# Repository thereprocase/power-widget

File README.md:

# Power Widget

**Canonical KiCad schematic.** This image is exported from the [native editable schematic](hardware/bench-rev-a/power-widget-bench.kicad_sch). The [earlier drawing was a layout mockup](hardware/bench-rev-a/layout-mockup.svg), not a KiCad export or the design authority.

**Reusable agent prompt, including the original inspiration:**

> think through the layout and topology from the perspective of a brilliant 1980s electrical engineer who stayed current on everything straight through to 2026. use his brain to architect the sheet and make it gorgeous
>
> Create a complete, flat, single-sheet schematic from this project's authoritative circuit data. Make the page explain the circuit: power and signal flow, measurement branches, isolation boundaries, supplies and service controls. Use traditional electrical symbols, continuous wires, explicit junction dots and unambiguous crossings: wire hops where supported, otherwise the native tool’s undotted-crossing convention. Keep every component and numbered pin accounted for; annotate wires with net names instead of replacing connections with labels. Preserve the circuit exactly. Use deliberate placement, readable typography and restrained color, with the clarity of a classic service-manual foldout. Verify connectivity against the source, export a zoomable SVG and printable PDF, put the image at the top of the README, and commit and push the result.
>
> Use conventional schematic symbols that engineers recognize on sight: ANSI-style zigzag resistors; parallel-plate nonpolarized capacitors and explicitly marked polarized capacitors; coil inductors; diode anode/cathode symbols with the cathode bar; LEDs with outward light arrows and photodiodes with inward light arrows; normally open or normally closed switch contacts shown in their unactuated state; connector pins, jumper links and test points; four-terminal Kelvin shunts with separate force and sense terminals; and, where present, BJT base/collector/emitter and emitter arrows, MOSFET gate/drain/source and body diodes, and op-amp triangles with +/− inputs. Use functional IC rectangles with named and numbered pins. Distinguish signal common, chassis ground and protective earth; preserve separate isolated returns. Use these symbols only for the devices and functions actually present. Verify each symbol's device type, terminal mapping, polarity, arrow direction and default state against the circuit data and the manufacturer's pinout. Rotate or mirror symbols only while preserving their electrical meaning. A wire crossing is not a junction unless explicitly dotted; a graphic must never imply an unintended connection. Check the rendered drawing as well as its underlying netlist.
>
> Implement the layout in the canonical, editable source of the design system this project actually uses: for KiCad, the native schematic in the existing KiCad project. Preserve component identities, footprints, pin mappings and PCB associations. Export the README image and PDF directly from that native source, and run the design system's electrical checks plus schematic-to-PCB consistency checks. Ensure the normal regeneration workflow cannot overwrite the native design with a competing source of truth. A separately drawn SVG or diagram is only a mockup, even if its netlist matches; label any intermediate mockup explicitly and do not present it as the canonical schematic.
>
> Make component identity and wire continuity obvious. Prefer one physical component in one location. If splitting a component improves the page, use the convention of a civil-engineering matchline: ghost the omitted portion at each location, mark the matchline, and add explicit reciprocal notes naming the other section and exactly where to look. Never leave the reader to infer that two symbols are one part or guess where a connection went. Use small cloud callouts to explain potentially confusing features; keep annotations visually distinct from electrical symbols and wires.
>
> Keep all lettering clear of conductors: never run a wire through a net name, reference, value, pin label or note. Place ordinary wire labels above or beside the wire with visible clearance; put boxed net tags on short annotation stubs in open space. Preserve the continuous main wire and use an explicit junction at each stub. Check the actual native export, not just the underlying coordinates or netlist. Visually inspect every functional section at readable magnification, including both ends of each connection, pin numbers, component values, junctions, crossings, polarity, symbol orientation and callouts. Then review the whole sheet for flow and consistency. Keep lettering clear of other lettering, symbol graphics (including LED arrows), and dashed graphical boundaries too. Add automated rendered-text/wire and text/text overlap checks where possible, and fix every collision before publishing.

**The whole circuit on one sheet:** [native SVG export](hardware/bench-rev-a/single-sheet.svg) · [printable A2 PDF](hardware/bench-rev-a/single-sheet.pdf) · [drawing notes and reproduction](hardware/bench-rev-a/README.md#single-sheet-schematic). All 82 physical components and 65 named nets. Each component appears once, including the complete J1 and P1 connectors. Dots identify connections; undotted crossings do not connect. Cloud notes explain the through path and Kelvin sensing.

An inline USB-C power monitor with isolated PC reporting. Preserve the original charger and cable negotiation while measuring voltage, current, watts and Wh.

**Newest design: [bench revision A native KiCad project](hardware/bench-rev-a/README.md).** It includes the sensing circuit, isolated USB reporting, STM32 firmware/debug access, assigned footprints and a routed bench PCB. Native KiCad checks report **zero ERC violations, DRC violations, unconnected items and schematic/PCB mismatches**. See the [layout review](docs/layout-review.md) for evidence and open gates. **The selected USB population is 5 A maximum; the project’s 9 A USB assembly is still a sourcing and qualification gate.**

## Board preview and drawings

Actual KiCad 2D plot of the **125 × 107 mm** bench PCB. The reporting USB-C port is on the lower long edge. This is an unbuilt prototype design; no 3D assembly render or hardware photographs are available yet.

| View | Contents |
|---|---|
| [PCB views](hardware/bench-rev-a/README.md#pcb-views) | Top and bottom copper plots from the routed board |
| [Circuit drawings](hardware/bench-rev-a/README.md#circuit-drawings) | Canonical single-sheet KiCad schematic, native exports and layout notes |
| [Architecture diagram](docs/architecture.md#two-power-domains-and-a-passive-main-path) | Transparent power path, sensing and isolated PC reporting |
| [Editable KiCad project](hardware/bench-rev-a/power-widget-bench.kicad_pro) | Schematic, PCB and local symbol/footprint libraries in the same directory |

## Design target

| Item | Requirement |
|---|---|
| Voltage | 28 V DC; at least 33.6 V component design margin |
| Continuous current | **9 A target: documented laptop maximum 8.5 A + 0.5 A** |
| Current design margin | **10.8 A: 1.20 × the 9 A target** |
| Inline data | USB 2.0; retain other contacts for charging transparency |
| Power accuracy | ±1% of reading at ≥5 W; ±5% from 0.5 W to below 5 W |
| Acquisition | About 58 fresh pairs/s, time-weighted one-second V/A/W reports and accumulated Wh |
| Reporting | Isolated USB-C on a long edge; timestamped serial, optional PC MQTT/HTTP forwarding |
| Product | Cheap but good; no display, battery or standalone logger required |

The selected [Apple/Dell/Lenovo laptop roster](docs/manufacturer-modes.md) drives the target. Extreme proprietary phone charging is excluded. The original 10 A/full-EPR and later 6 A specifications are superseded; voltage remains 28 V. No physical assembly is qualified yet.

## Early open question: captive male or two receptacles?

**Captive male is the bench baseline; final product topology remains open.** The original charger cable enters one receptacle, and a short custom captive plug extends its contacts to the device. The separate PC receptacle is on a long edge. OEM MagSafe/slim-tip cables may require charger-side placement and different energy accounting.

Two inline receptacles remain an allowed outcome if their orientation and cable-discovery behavior can be made transparent. Fixed CC wiring between two ordinary C-to-C cables fails some orientations; the [contact map and truth table](docs/connector-routing.md) explain the constraint. A generic cut cable is not a qualified captive assembly.

## Bench circuit and calculated feasibility

INA228 measures a 5 mΩ four-terminal high-side shunt. An inline LDO powers sensing; a PC-powered STM32F072CBT6 communicates through isolated I²C. The board includes SWD, UART, GPIO, force/Kelvin access and selectable floating sensor power. Dedicated links support measuring board consumption. Original charging contacts have no inline PD controller or substituted contract.

| Calculation | Preliminary result |
|---|---|
| Largest one-second DC error allocation, ≥5 W | **0.874%**, at 28 V / 5 W |
| Largest one-second DC error allocation, 0.5–<5 W | **4.539%**, at 28 V / 0.5 W |
| Sensor window / reporting | **17.28 ms / one second** |
| Added hot loop resistance, captive study | **14.879 mΩ** against a 15 mΩ target |
| Shunt heat at 9 A / 10.8 A | **0.405 W / 0.583 W** nominal |

These are engineering allocations, not measured specifications. One-second noise, dynamic energy accuracy, thermal behavior and connector performance require physical validation. A board-output reading needs a downstream cable correction before being called laptop-input energy.

## Design package

| Read | Purpose |
|---|---|
| [Design brief](docs/design-brief.md) | Current requirements and assumptions |
| [Bench hardware](hardware/bench-rev-a/README.md) | Circuit sheets, component schedule, jumpers and bring-up |
| [Manufacturer modes](docs/manufacturer-modes.md) | Primary laptop evidence and rating rule |
| [Connector wiring](docs/connector-routing.md) | Contact map and orientation proof |
| [Architecture](docs/architecture.md) / [decisions](docs/decisions.md) | Components, domains and unresolved gates |
| [Calculated budgets](analysis/results.md) / [method](docs/budgets.md) | Accuracy, loss, timing and assumptions |
| [Firmware contract](firmware/README.md) | MCU pins, sensor registers, timestamped serial and integration plan |
| [Energy comparison](docs/energy-comparison.md) | Matching intervals, board consumption, cable correction and uncertainty |
| [Validation](docs/validation-plan.md) / [cost and build](docs/cost-and-build.md) | Prototype qualification and planning allowances |
| [Research record](docs/sources.md) / [progress](docs/progress.md) | Sources, evidence gaps and checkpoints |

## Reproduce

```sh
python tools/budgets.py --check
python tools/orientations.py --check
python tools/capture_bench.py --check
python tools/draw_flat_schematic.py --check
```

Omit `--check` to regenerate. The budget and orientation tools use the Python standard library. Native schematic export/check commands require KiCad 9+ and librsvg; see [CAD reproduction](hardware/bench-rev-a/README.md#single-sheet-schematic). The budget sweep covers 19,635 settled operating points at the 9 A target. `capture_bench.py` exports and validates native pin/net data; `draw_flat_schematic.py` also runs KiCad ERC and PCB DRC with schematic parity.

## Next gate

Review the routed PCB against a fabricator's stack and capabilities, finalize the orderable BOM and captive strain relief, and resolve protection/overrange behavior before fabrication release. Source and qualify the required 9 A USB assembly; the selected USB parts support only the 5 A bench population. Firmware can start on the documented interfaces while these gates close. Physical validation must establish thermal capacity, measurement accuracy and OEM charging compatibility. Earlier designs remain in commit history.

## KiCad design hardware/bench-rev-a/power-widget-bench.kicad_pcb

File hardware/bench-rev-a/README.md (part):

# Bench revision A — native schematic and PCB

**28 V / 9 A continuous design target, 10.8 A design margin. No physical assembly is qualified.** This is the accessible prototype for connector experiments, calibration and MCU firmware development. It contains the complete proposed sensing, reporting, supply and debug circuits rather than a separate continuity fixture.

Open [power-widget-bench.kicad_pro](power-widget-bench.kicad_pro) in KiCad 9. The project includes the [native schematic](power-widget-bench.kicad_sch), [editable PCB](power-widget-bench.kicad_pcb), project symbols, and a snapshot of all 23 used footprint types. Native checks report **zero [ERC violations](erc.rpt), [DRC violations, unconnected items and schematic/PCB mismatches](drc.rpt)**. Read the [layout review](../../docs/layout-review.md) for board status and release gates. There are no fabrication-release Gerbers.

## PCB views

These are actual 2D plots exported from the checked-in KiCad PCB. No 3D assembly render or physical prototype photograph is available yet.

[Open top view](pcb-top.svg) — front copper with front silkscreen and outline.

<details>
<summary>Show bottom copper view</summary>

[Open bottom copper view](pcb-bottom.svg) — bottom copper with front silkscreen and outline, **viewed from the top**. This is not a mirrored bottom assembly drawing.

</details>

## Circuit drawings

### Single-sheet schematic

[Native SVG export](single-sheet.svg) · [A2 PDF](single-sheet.pdf) · [Editable schematic](power-widget-bench.kicad_sch) · [Native checks](single-sheet-check.json)

**This is the canonical KiCad schematic, not a separately drawn diagram.** The SVG and PDF are direct `kicad-cli` exports. The README PNG is only a white-background rasterization of that SVG so it remains readable in light and dark themes. The [earlier layout mockup](layout-mockup.svg) is retained as a reference, explicitly not the design authority. The former five-sheet schematic is superseded and remains available in Git history.

The force path runs left to right through R1, with its Kelvin measurement branch directly beneath it. Every J1 and P1 contact is visible in its **one complete connector symbol**. Isolated I²C crosses the marked boundary into the PC-powered reporting circuit. Cloud callouts explain the through path and the shunt's separate force and sense terminals. Every connection is wired continuously. Each net is named once on a short annotation stub, with visible clearance between the tag and conductors. The main wire remains continuous and the stub has an explicit junction. Dots mean junctions; undotted crossings are not connected. Unconnected pin numbers and their no-connect crosses appear inside the relevant packages. There are no off-sheet connections or split component units in this version.

KiCad reports **82 physical components, 65 named nets, 288 connected numbered pins and 30 unconnected numbered pins**. Six additional nonphysical power flags stay in the native schematic for ERC. The [migration comparison](native-migration-check.json) verifies unchanged pin/net connectivity, values, footprints and component UUIDs against the previous native design. PCB edits only flatten the 82 schematic association paths; copper, placement and all other PCB content are unchanged. Native [ERC](erc.rpt), [DRC and schematic/PCB parity](drc.rpt) pass with zero violations or unconnected items.

**Edit `power-widget-bench.kicad_sch` in KiCad.** The local `Bench.kicad_sym` library contains editable native symbol geometry; symbols are also embedded in the schematic. Reference, Value and Footprint are native fields. The auxiliary Domain, Section, CircuitKind, SourceFootprint and Notes fields supply metadata for the JSON and component-schedule exports. The historical JSON `sheet` field now identifies a functional placement group, not a separate schematic sheet.

The normal workflow flows in one direction: **native schematic → native netlist / JSON / schedule / SVG / PDF / PNG**. Neither export script writes a schematic, library or PCB. There is no separate Python circuit definition that can overwrite edits made in KiCad.

```sh
python tools/capture_bench.py             # export JSON and component schedule from KiCad
python tools/draw_flat_schematic.py       # run ERC/DRC/parity and export drawings
python tools/capture_bench.py --check     # verify native data exports are current
python tools/draw_flat_schematic.py --check
```

Use KiCad 9.0.9 and librsvg (`rsvg-convert`) to reproduce the checked-in exports. `KICAD_CLI` can name a local CLI executable. If no local KiCad CLI is found, the tools use Docker and the pinned [official KiCad container](https://gitlab.com/kicad/packaging/kicad-docker) for 9.0.9 in [kicad_native.py](../../tools/kicad_native.py); only the project directory is mounted, and the container runs as the invoking user without network access. `KICAD_DOCKER_IMAGE` can select another installed image. The exporter checks the actual plotted glyph bounds of all visible lettering—including all 65 net labels, references, values, pin labels and notes—against every native wire and against other lettering, rejecting wire/text and text/text collisions. Visual review additionally covers symbol graphics, dashed boundaries, and every functional section at readable magnification. The SVG check ignores only KiCad's export timestamp; the PDF, PNG and native reports have recorded hashes. Print the PDF at A2 or enlarge it, or zoom the vector files on screen.

These are CAD consistency results, not hardware qualification. The existing component, connector and fabrication gates still apply.

## Bench arrangement

The bench PCB is **125 × 107 mm**, four layers, with a candidate 2 oz outer / 1 oz inner stack. The force path runs across the upper portion. The PC receptacle sits on the bottom long edge, and a 3 mm copper keepout separates PC and inline domains across every layer. U2 bridges the gap; the ground plane is split by domain. This is functional isolation, not a certified insulation rating. Fabricator capability, thermal behavior and USB signal integrity require qualification.

J1 is the selected GCT inline receptacle; P1 is the board-side solder termination for a custom captive harness. Its individual contact wiring is defined in [connector-routing.md](../../docs/connector-routing.md). All CC-contact, SBU and SuperSpeed contact paths are retained; only USB 2.0 data performance is in scope. No inline PD controller, new e-marker, or charger-identification termination is fitted. The selected GCT USB population is limited to **5 A**. See [connector selection](../../docs/connector-selection.md); the 9 A USB assembly remains unsourced. Final product topology remains open.

| Access | Connections / use |
|---|---|
| J2 / J3 | Two-pin force connections: 1 = VBUS_A / VBUS_B, 2 = GND_INLINE. Electrically parallel with USB ports; use qualified terminals and short heavy leads. |
| J4 | 1 = upstream shunt Kelvin, 2 = downstream shunt Kelvin, 3 = PCB_B voltage, 4 = quiet inline ground. Sense only. |
| TP4 / TP5 | Separate A5 / B5 contact probes. Use suitable high-impedance, low-capacitance isolated probes; no grounded PC wire. |
| J5 | PC-side I²C: 1 = GND_PC, 2 = switched 3.3 V reference, 3 = SCL, 4 = SDA. External open-drain master supported with U3 held in reset and JP4 fitted. |
| J6 | Inline I²C: 1 = GND_INLINE, 2 = 3V3_INLINE, 3 = SCL, 4 = SDA. Floating instruments only. |
| J7 | Floating external supply: 1 = 3.3 V input, 2 = GND_INLINE. Current limit for initial bring-up; never tie to PC ground. |
| J9 | Cortex 10-pin SWD, 1.27 mm, keyed pin 7 absent. Pin 1 is target-voltage reference; pin 6 has no SWO. |
| J10 | 3.3 V UART: 1 = GND_PC, 2 = board TX, 3 = board RX, 4 = supply reference. |
| J11 | GPIO: GND_PC, 3V3_PC, PA4, PA5, PA6, PA7, PB10, PB11 in pin order. |

Header supply pins are references/outputs except the explicitly identified J7 input. External debug probes must not inject supply power. Grounded bench supplies, scopes and electronic loads can externally join the domains even when the board itself is isolated.

## Jumpers and power accounting

| Link | Normal state | Bench purpose |
|---|---|---|
| JP1 | One shunt on 1–2 | Selects inline LDO. Move the single shunt to 2–3 for floating external J7 supply; never fit both. |
| JP2 | Fitted | Replace with an ammeter to characterize PC-domain consumption. Input capacitor, ESD and VBUS divider are ahead of this link; use a USB input-current measurement for total PC-port draw. |
| JP3 | Fitted | Replace with a floating ammeter to measure the inline regulator/sensor branch. R10 remains in circuit. |
| JP4 | Not fitted | Forces isolator PC supply on for an external I²C master. Remove for normal firmware/suspend testing. R26 limits conflict with PA1. |

U4 derives sensor power from VBUS_A before the shunt. JP3 measures the main self-consumption branch; output-sense loading remains a separate small burden. The current 8 mA allocation is **not** a measured correction. Characterize actual draw over voltage, activity and temperature, including the measuring instrument's burden. See [energy comparison](../../docs/energy-comparison.md).

U7 switches U2 side 1 and its pull-ups using MCU PA1. The ISO1641 side-1 high-state maximum is 3.2 mA at 3.3 V, so simply sleeping the MCU would leave an excessive suspend burden. Before disabling U7, firmware releases PB6/PB7 and removes internal pull-ups; resume enables the rail and waits for settling before I²C. This circuit addresses the identified load; total USB suspend current still needs measurement.

## Bring-up sequence on this board

1. Close the documented PCB/connector/protection release gates, then inspect the assembly unpowered. Verify PC/inline isolation, both independent CC paths and no supply shorts. Leave OEM equipment disconnected.
2. Power J8 only. Establish 3V3_PC, reset/boot/SWD and USB enumeration. Verify PA1 can switch the isolator rail and that suspend removes its load. Sensor absence is a valid diagnostic state.
3. Use current-limited floating 3.3 V at J7 with JP1 on 2–3. Verify INA228 ID, raw readings, calibration commands and logging while VBUS is zero. This permits firmware work before an inline charger is attached.
4. Apply current-limited 5 V through qualified J2/J3 force wiring and a small known load. Verify polarity, the B voltage reference, one-second statistics and energy. Return JP1 to 1–2 and repeat with normal sensor power. Compare the JP3 measurement with the supply budget.
5. Sweep voltage and load for calibration. Increase core current toward 9 A only with rated force connections, monitored temperatures and an appropriately limited supply/load. The 10.8 A point needs an explicit continuous-capacity thermal test; it is not a brief survival pulse.
6. Qualify the actual captive assembly electrically and thermally, then compare direct versus inserted OEM charging across all orientations. Keep the controlled bench at known ≤28 V until overrange handling is resolved.

## Before PCB release

J1 and the force terminals now have selected parts and footprints; P1 has a board-side captive-harness termination. The shunt's four terminals and native pad/net mapping have been reviewed. Complete the orderable BOM, passive voltage/power and capacitor bias/stability review, actual captive assembly and strain relief. The selected USB parts remain limited to 5 A; sourcing a qualified 9 A USB assembly is a separate open gate.

Review the routed board against the fabricator's stack, copper weight, fine clearances and USB impedance requirements. Resolve inline ESD/overrange protection without compromising CC or low-power leakage. Review unpowered behavior, USB timing/current and regulator thermals; physical tests must establish measurement accuracy, current capacity and charging compatibility. See the [layout](../../docs/layout-review.md), [connector](../../docs/connector-selection.md) and [protection](../../docs/protection-review.md) reviews for the remaining work.

Export circuit data from the native schematic with `python tools/capture_bench.py`; use `--check` to detect stale exports. Its assertions check independent CC nets, no shared PC/inline nets and the MCU supply pins. These checks do not replace ERC, impedance/thermal layout work or hardware tests.

## Physical-design reproduction

With KiCad 9 Python `pcbnew` available:

```sh
python tools/capture_bench.py
python tools/footprint_bench.py
python tools/layout_bench.py
python tools/fanout_bench.py
# Route the generated DSN with a compatible Specctra router; use one optimization thread.
python tools/finish_bench.py --session hardware/bench-rev-a/power-widget-bench.ses
# The retained session requires these reviewed manual repairs:
python tools/review_route_bench.py
python tools/finish_bench.py
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
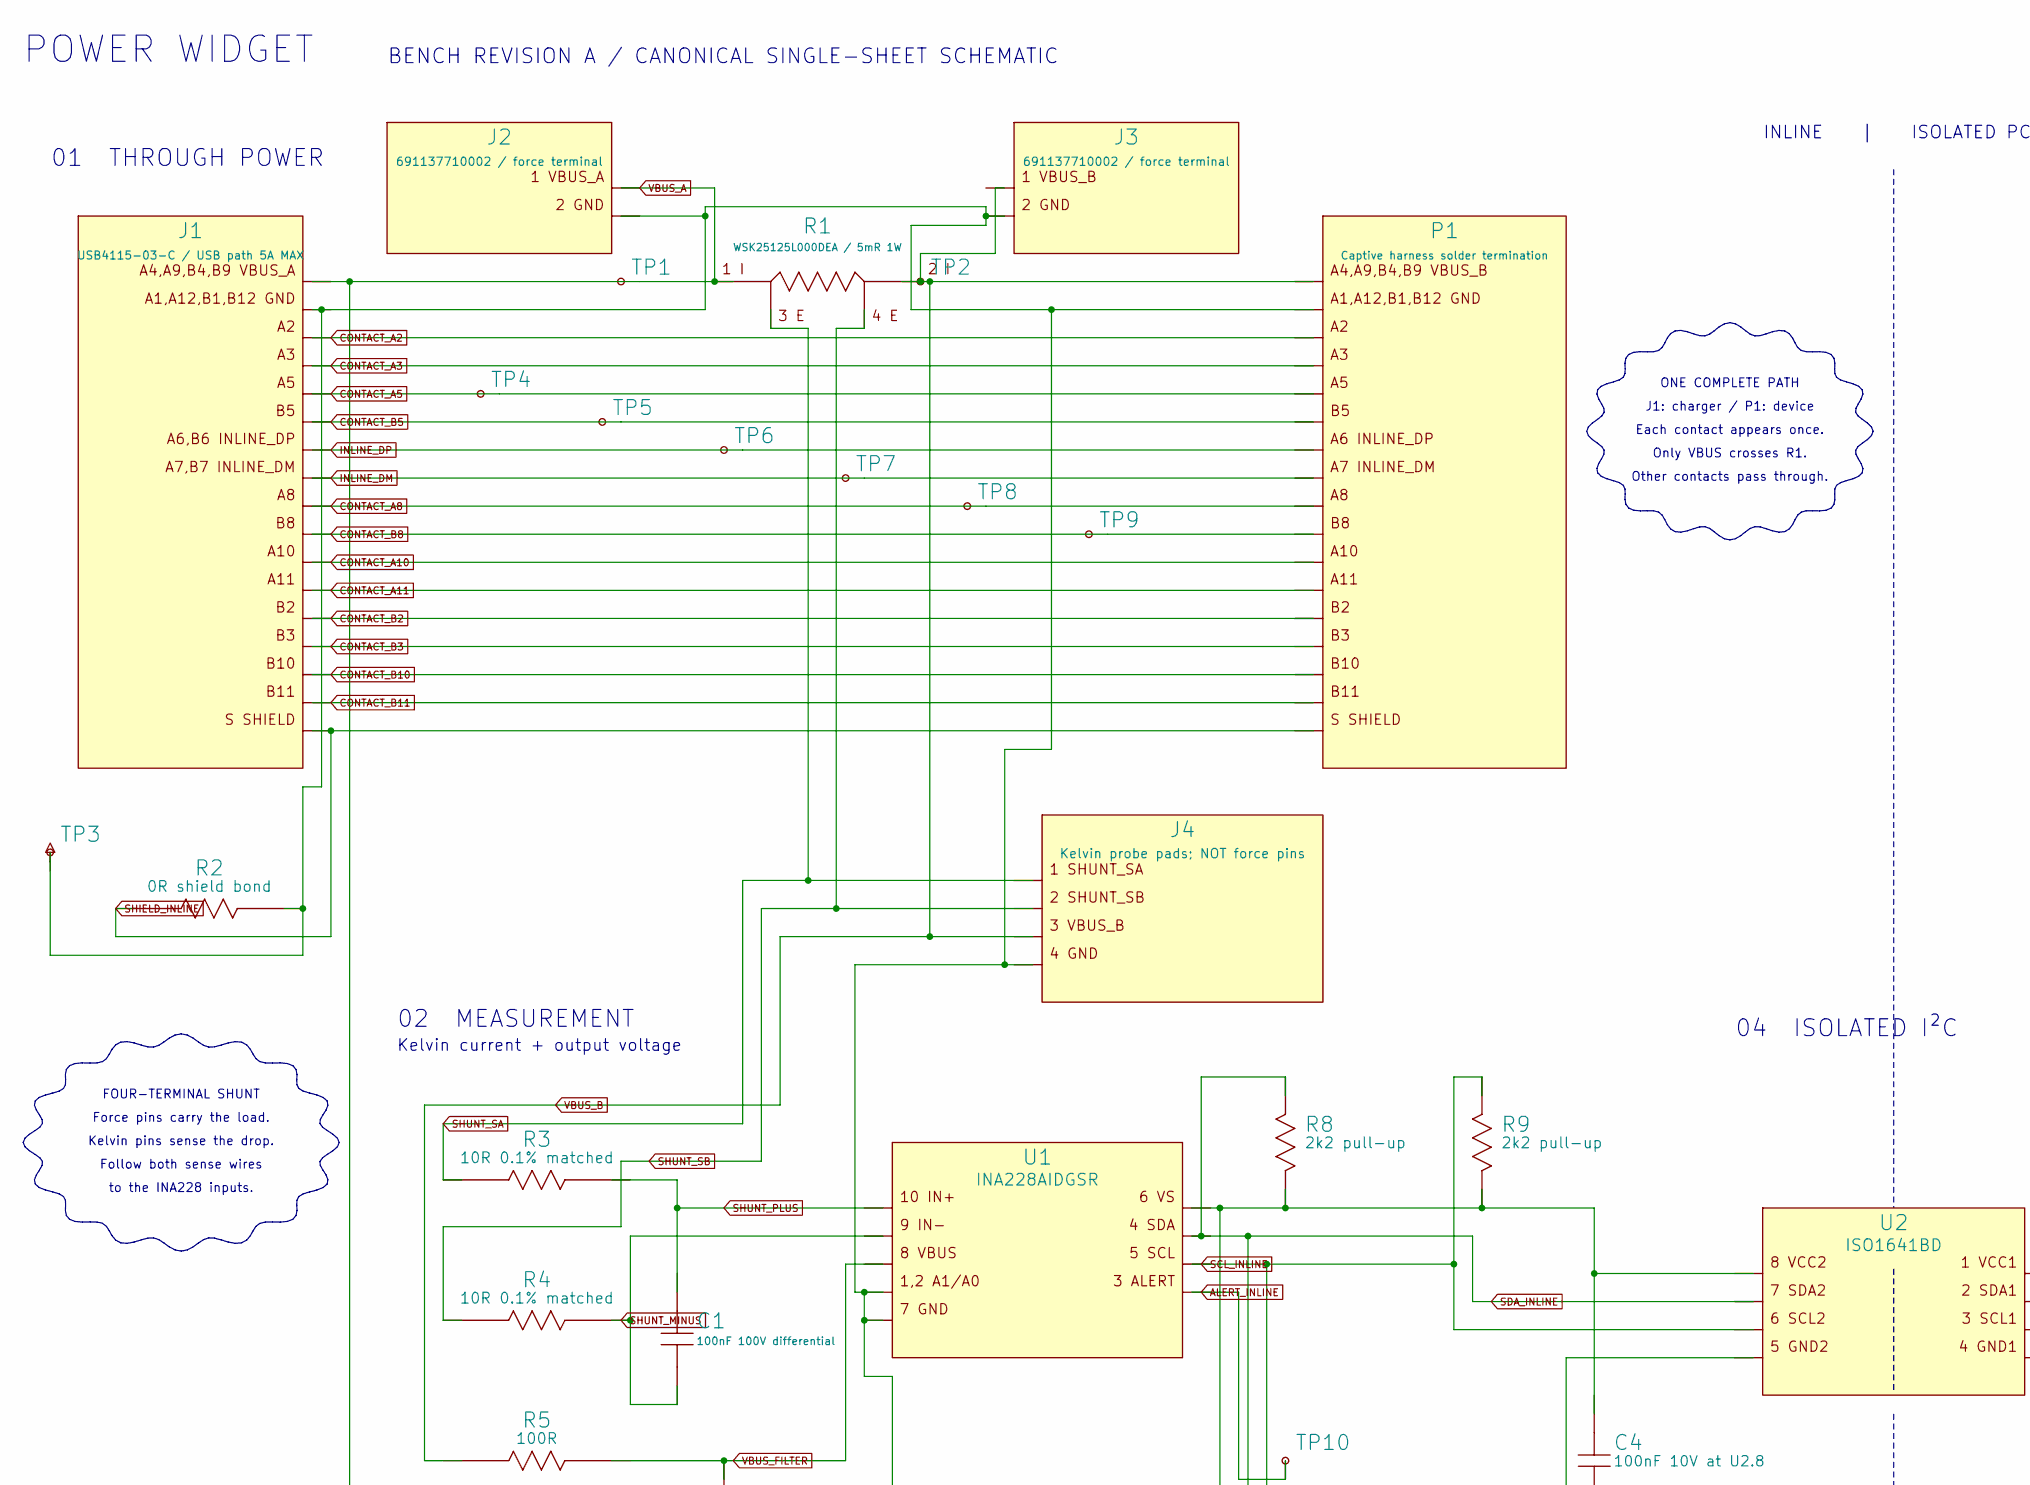
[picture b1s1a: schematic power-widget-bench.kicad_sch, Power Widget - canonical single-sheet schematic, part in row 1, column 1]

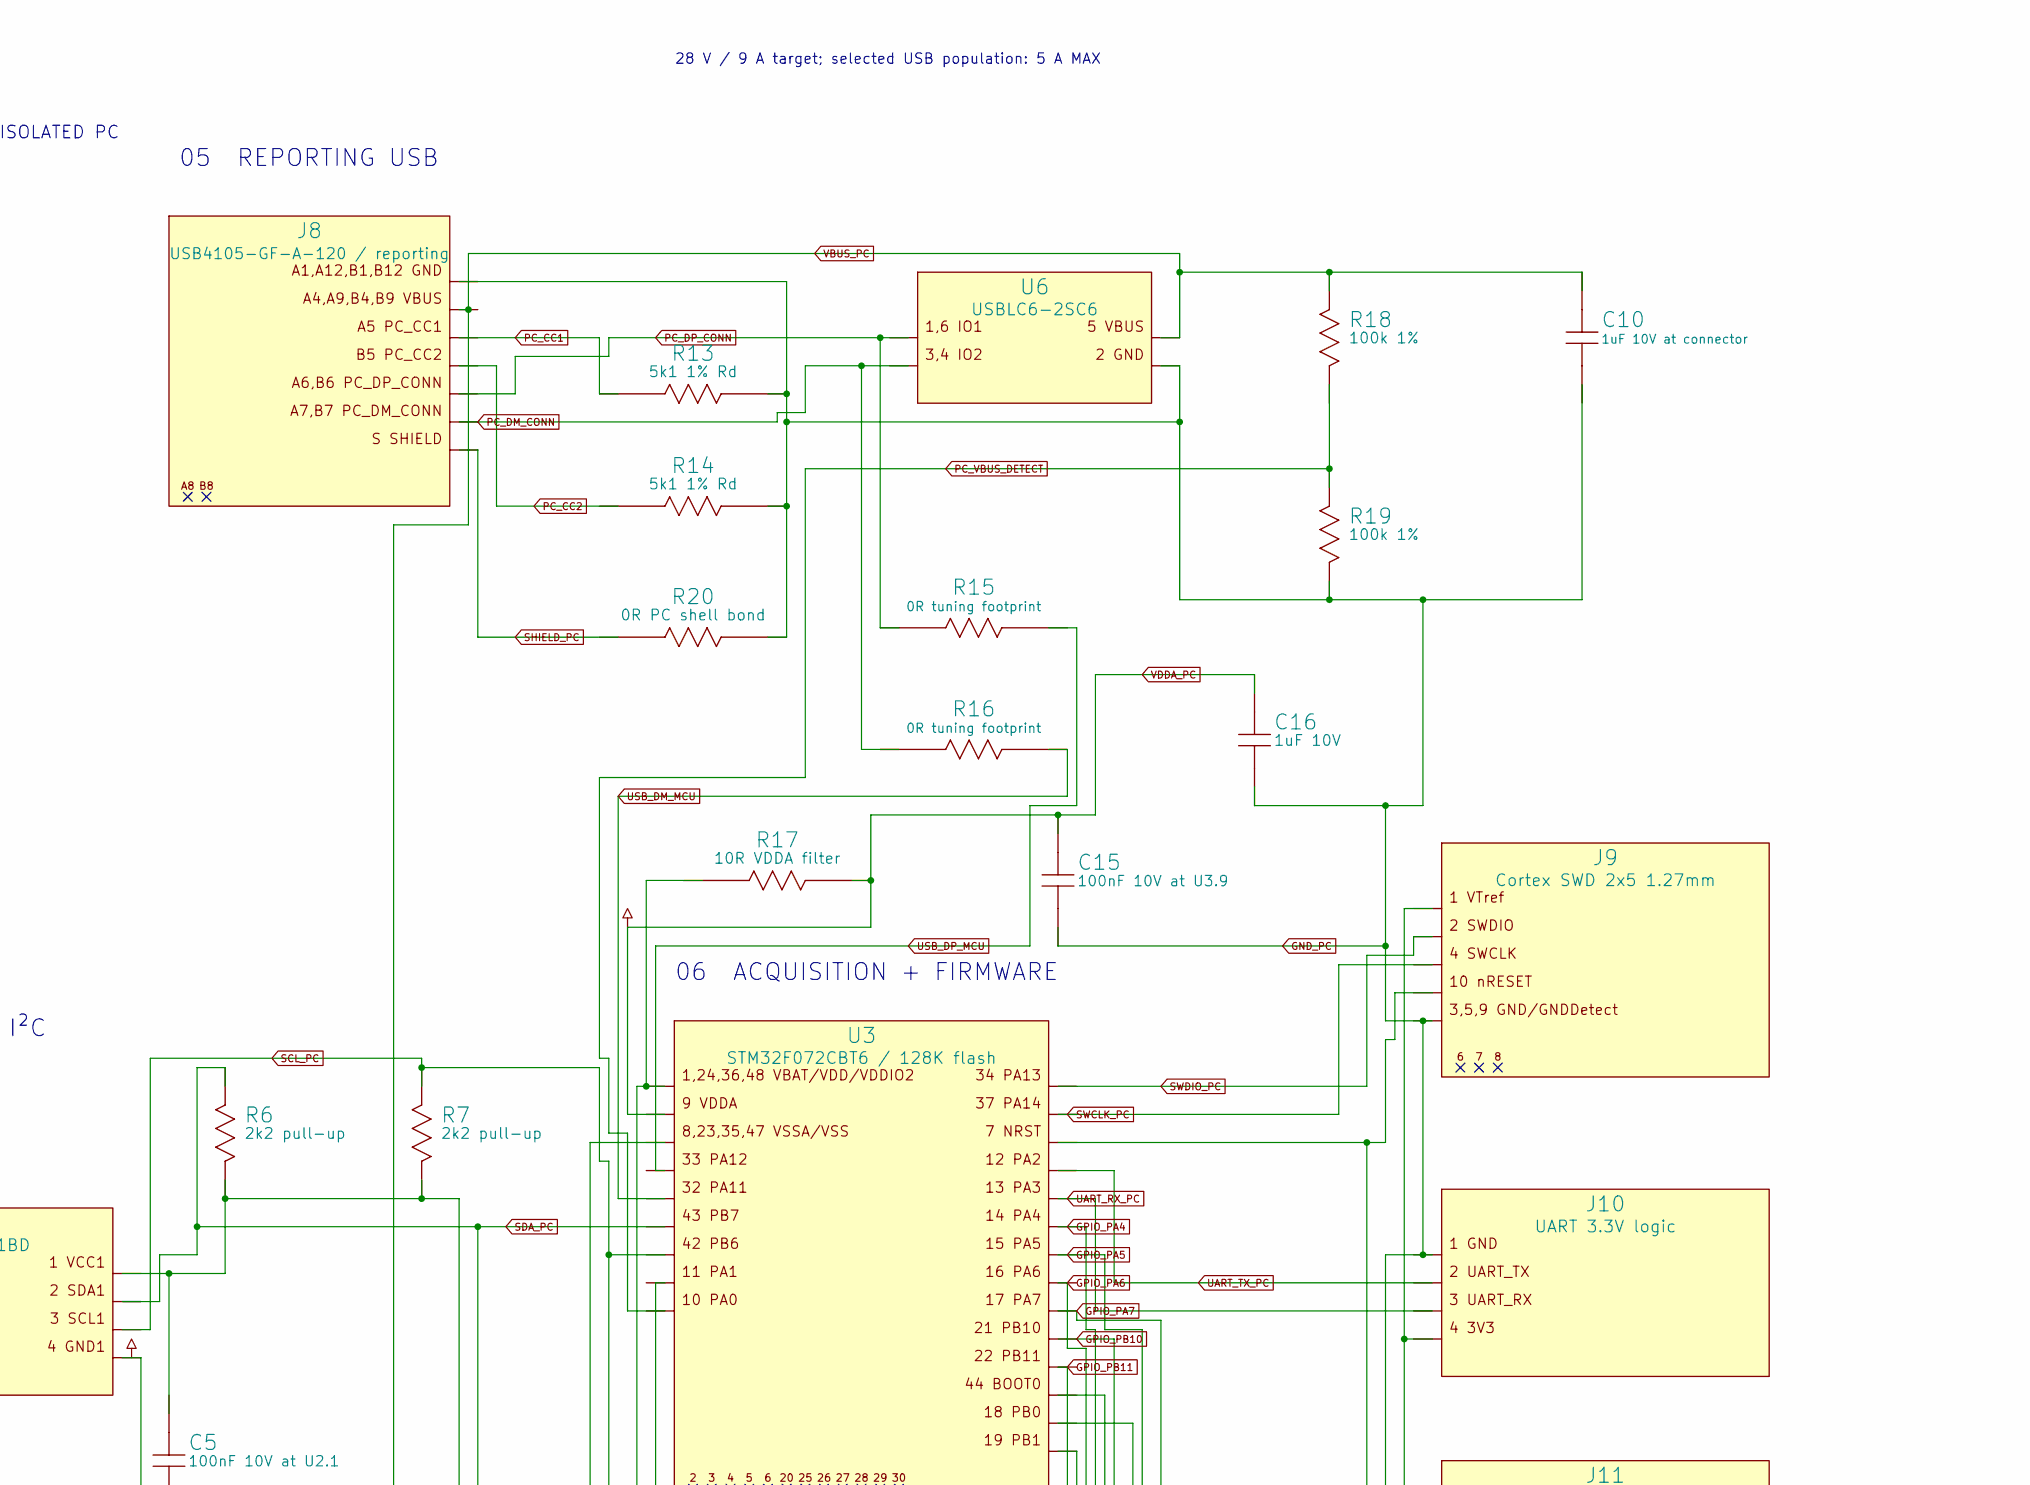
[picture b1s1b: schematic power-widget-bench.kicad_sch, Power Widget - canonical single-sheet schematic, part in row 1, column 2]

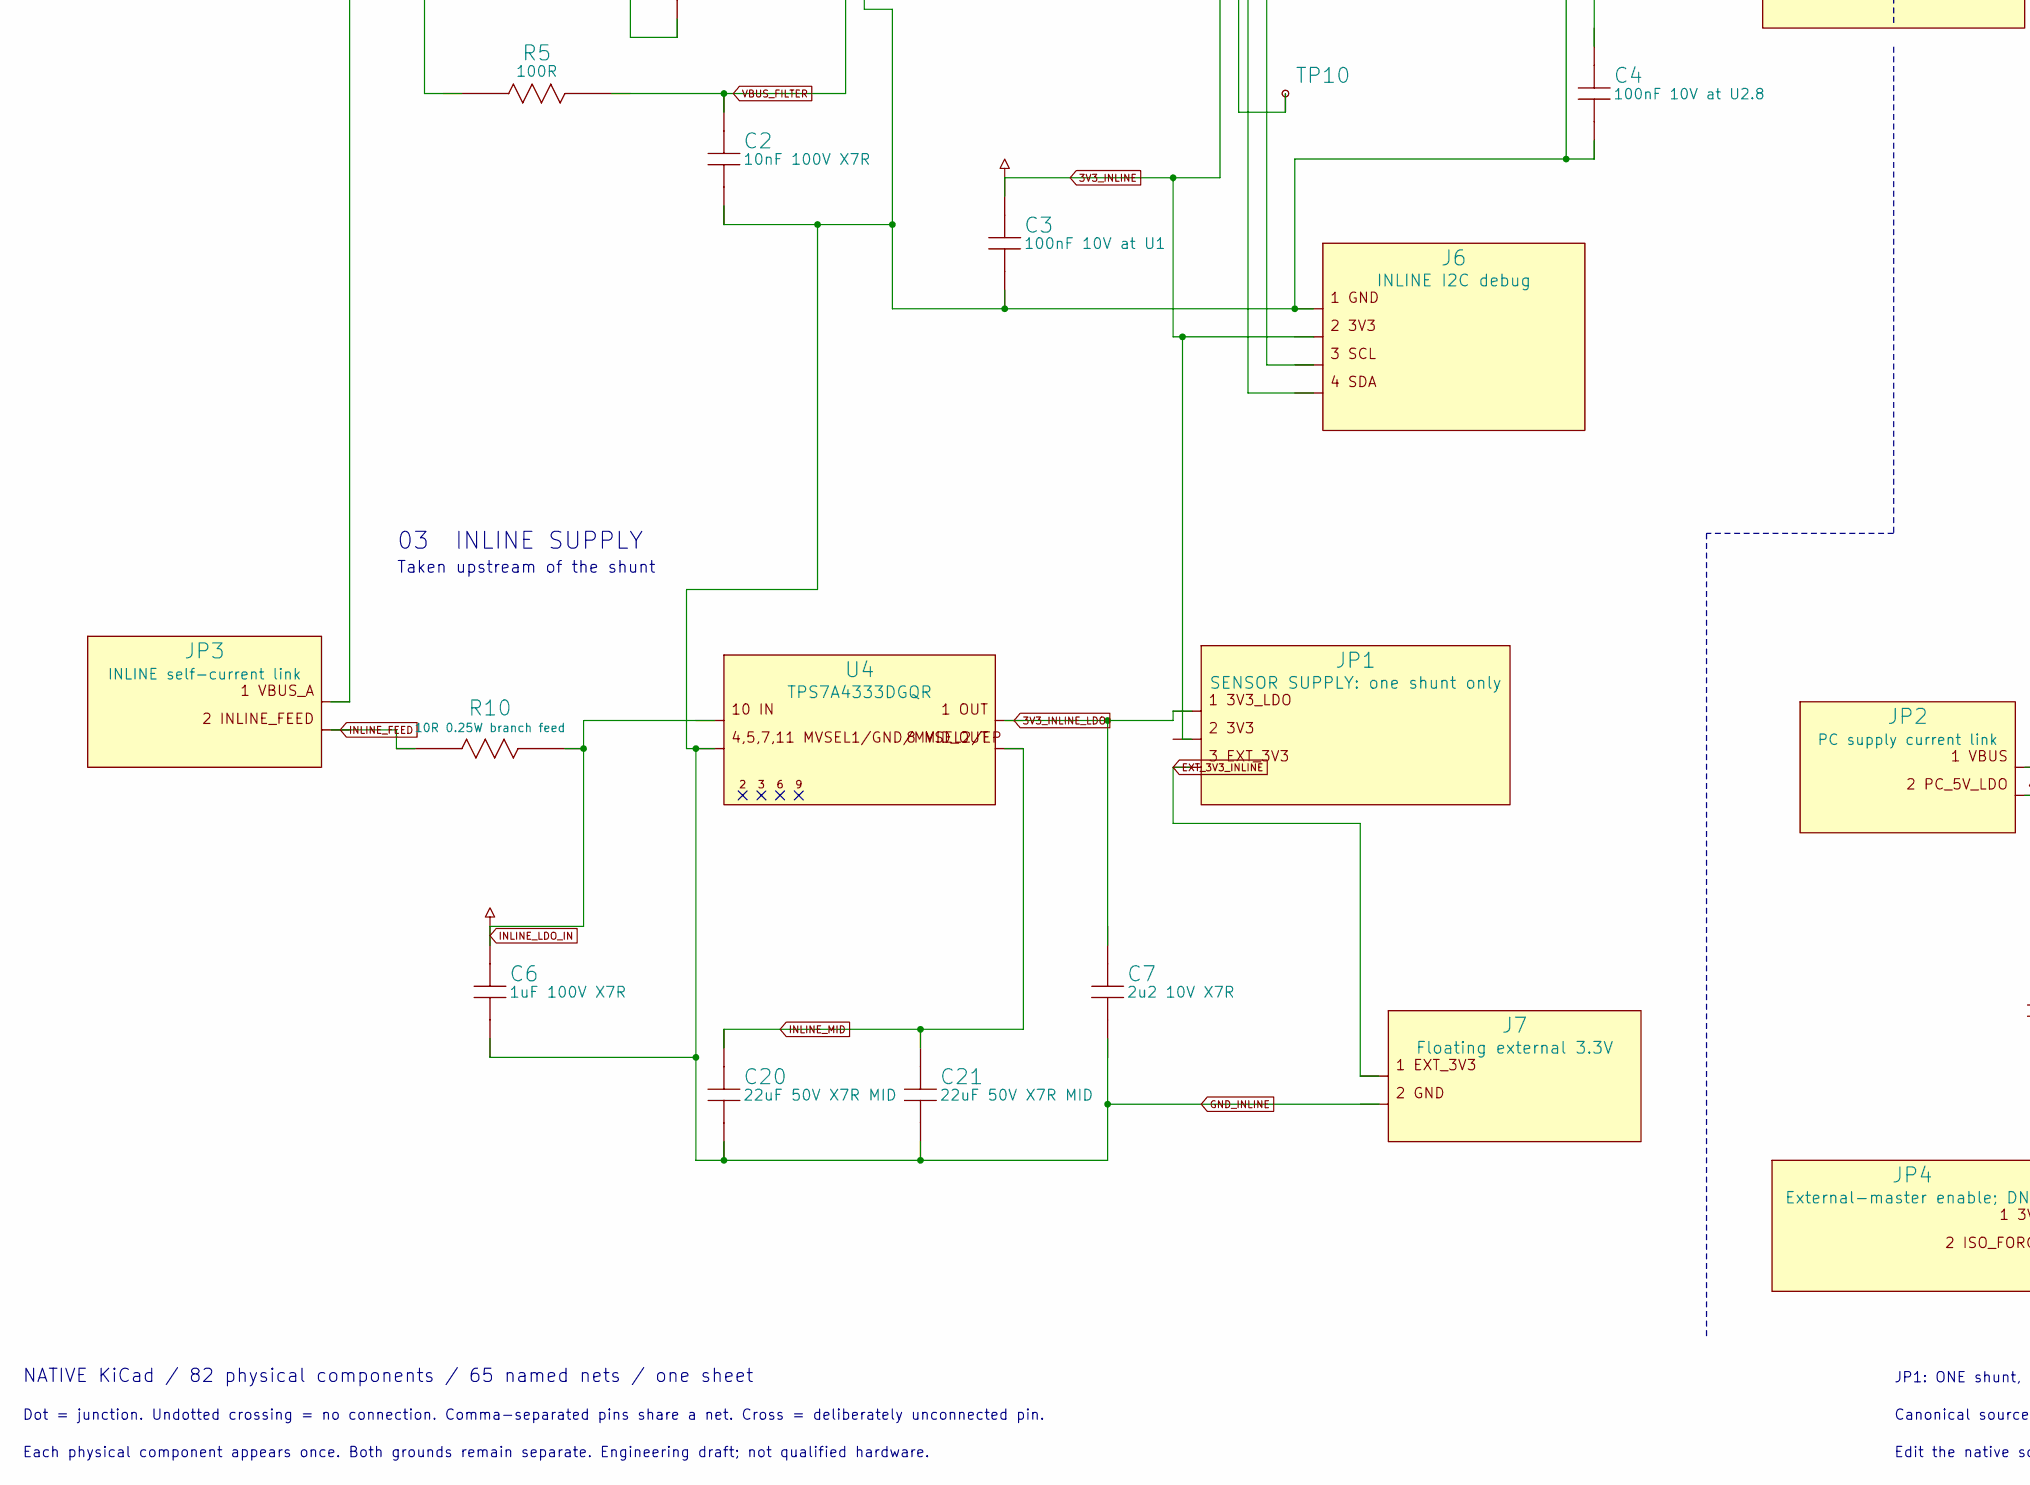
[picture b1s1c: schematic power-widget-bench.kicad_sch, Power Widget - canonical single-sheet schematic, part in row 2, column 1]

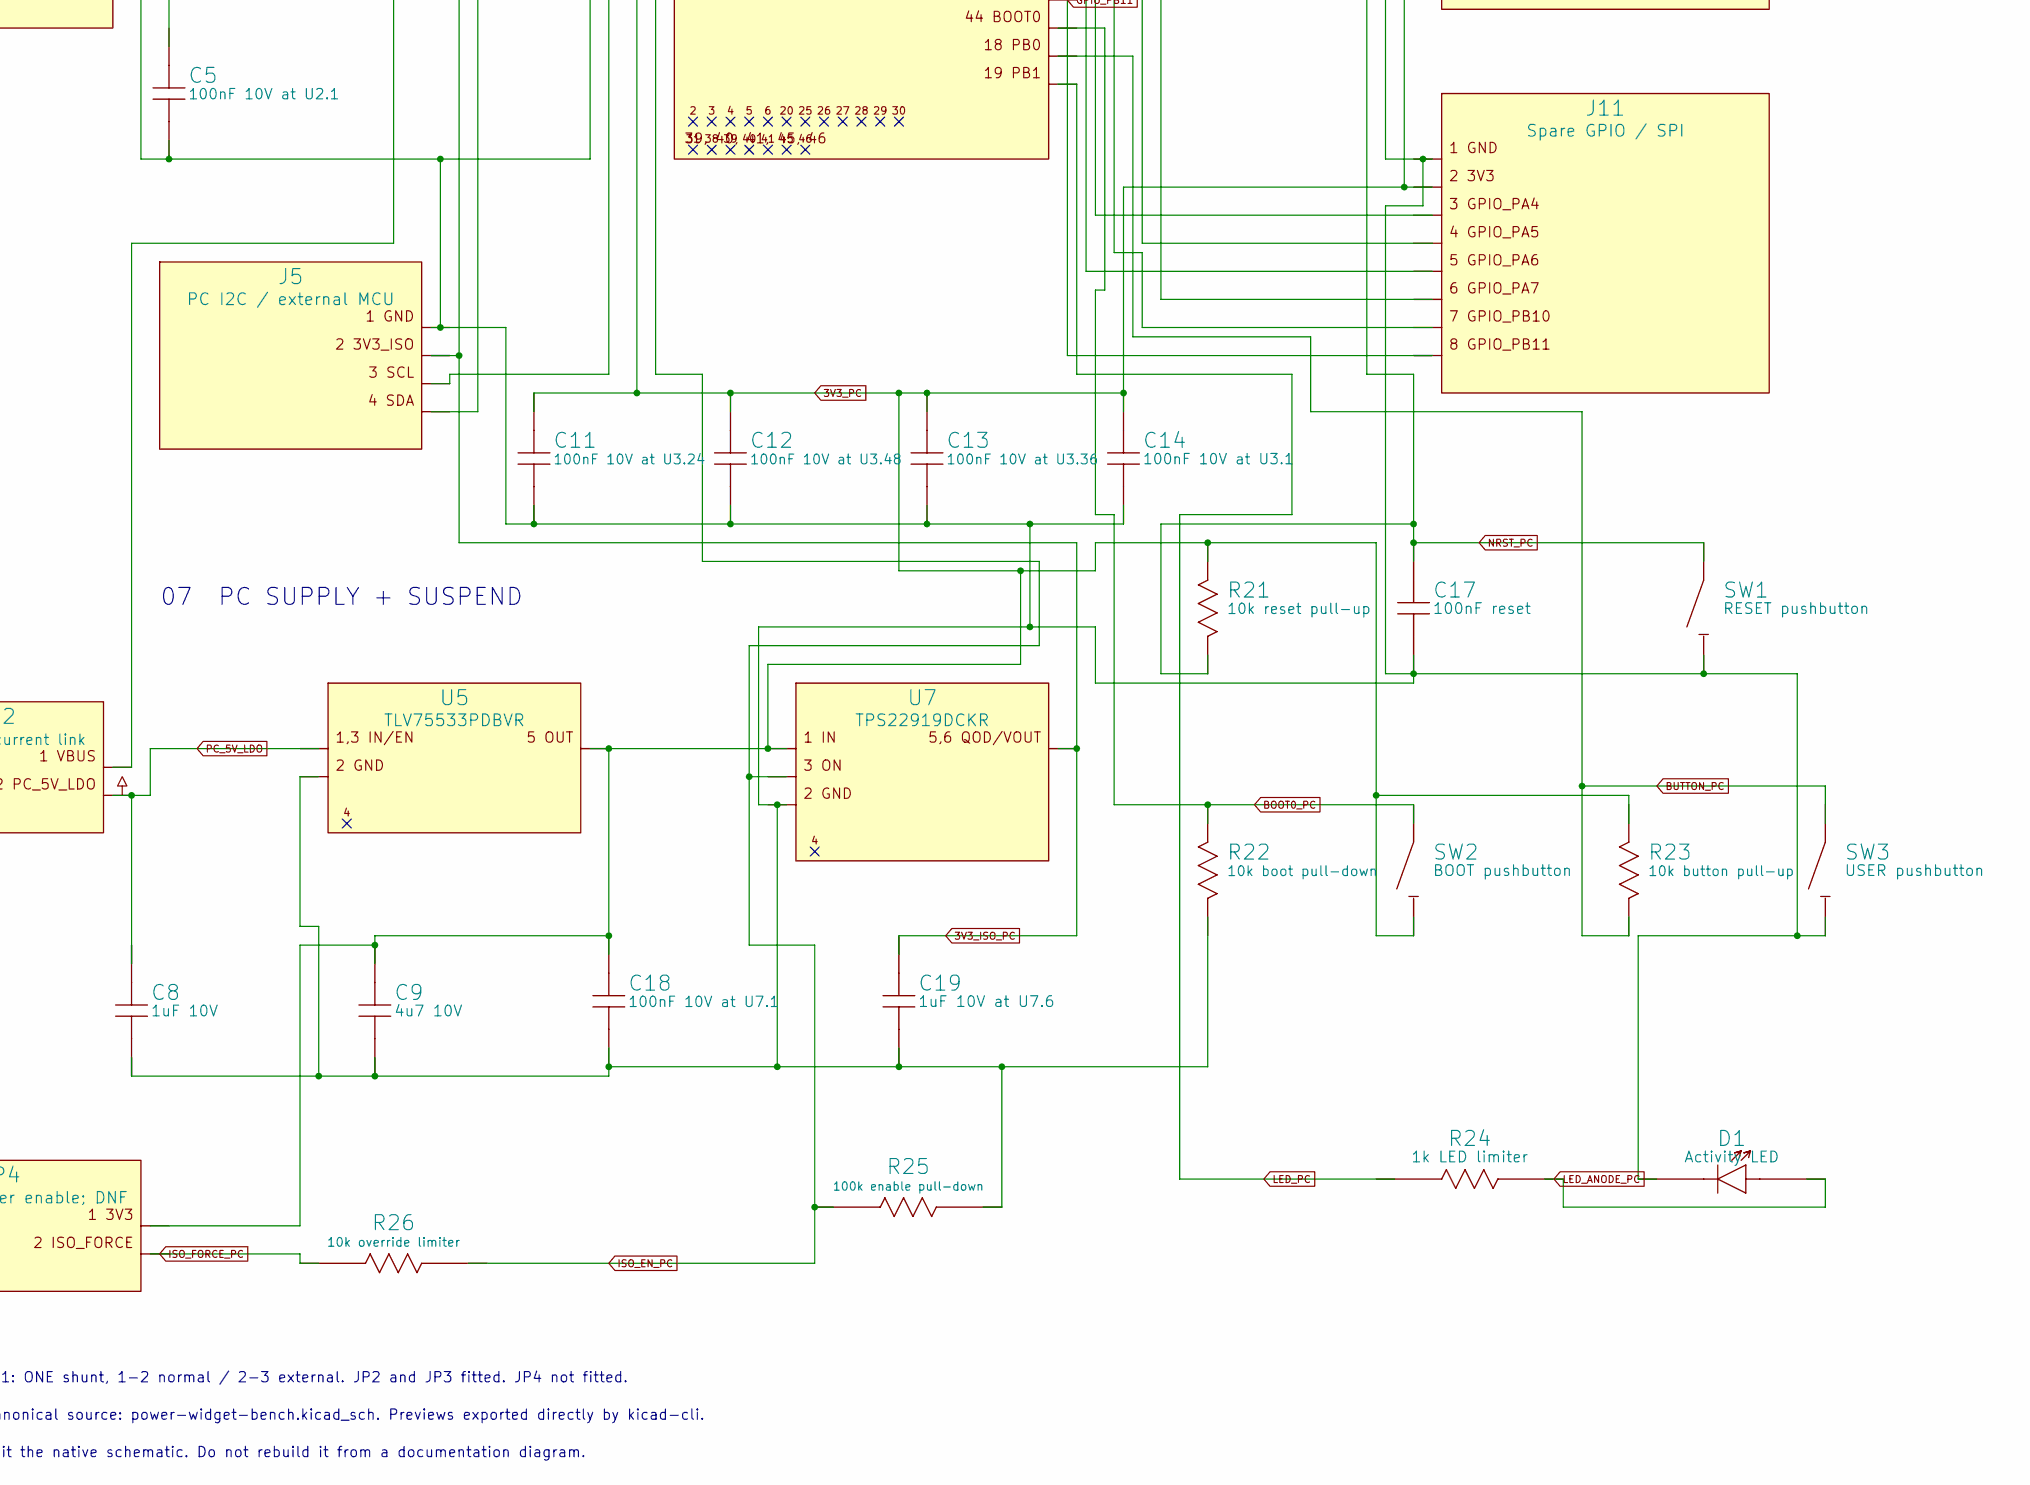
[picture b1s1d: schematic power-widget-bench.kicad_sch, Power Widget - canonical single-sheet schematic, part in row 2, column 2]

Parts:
C1: 100nF 100V differential; C_0805_2012Metric
C2: 10nF 100V X7R; C_0805_2012Metric
C3: 100nF 10V at U1; C_0805_2012Metric
C4: 100nF 10V at U2.8; C_0805_2012Metric
C5: 100nF 10V at U2.1; C_0805_2012Metric
C6: 1uF 100V X7R; C_1210_3225Metric
C7: 2u2 10V X7R; C_0805_2012Metric
C8, C16: 1uF 10V; C_0805_2012Metric
C9: 4u7 10V; C_0805_2012Metric
C10: 1uF 10V at connector; C_0805_2012Metric
C11: 100nF 10V at U3.24; C_0805_2012Metric
C12: 100nF 10V at U3.48; C_0805_2012Metric
C13: 100nF 10V at U3.36; C_0805_2012Metric
C14: 100nF 10V at U3.1; C_0805_2012Metric
C15: 100nF 10V at U3.9; C_0805_2012Metric
C17: 100nF reset; C_0805_2012Metric
C18: 100nF 10V at U7.1; C_0805_2012Metric
C19: 1uF 10V at U7.6; C_0805_2012Metric
C20, C21: 22uF 50V X7R MID; C_1210_3225Metric
D1: Activity LED; LED_0805_2012Metric
J1: USB4115-03-C / USB path 5A MAX; USB_C_Receptacle_GCT_USB4115-03-C
J2, J3: 691137710002 / force terminal; Force_5mm_2pin
J4: Kelvin probe pads; NOT force pins; PinHeader_1x04_P2.54mm_Vertical
J5: PC I2C / external MCU; PinHeader_1x04_P2.54mm_Vertical
J6: INLINE I2C debug; PinHeader_1x04_P2.54mm_Vertical
J7: Floating external 3.3V; PinHeader_1x02_P2.54mm_Vertical
J8: USB4105-GF-A-120 / reporting; USB_C_Receptacle_GCT_USB4105-xx-A_16P_TopMnt_Horizontal
J9: Cortex SWD 2x5 1.27mm; PinHeader_2x05_P1.27mm_Vertical
J10: UART 3.3V logic; PinHeader_1x04_P2.54mm_Vertical
J11: Spare GPIO / SPI; PinHeader_1x08_P2.54mm_Vertical
JP1: SENSOR SUPPLY: one shunt only; PinHeader_1x03_P2.54mm_Vertical
JP2: PC supply current link; PinHeader_1x02_P2.54mm_Vertical
JP3: INLINE self-current link; PinHeader_1x02_P2.54mm_Vertical
JP4: External-master enable; DNF; PinHeader_1x02_P2.54mm_Vertical
P1: Captive harness solder termination; Captive_Termination
R1: WSK25125L000DEA / 5mR 1W; WSK2512_5mR
R2: 0R shield bond; R_0805_2012Metric
R3, R4: 10R 0.1% matched; R_0805_2012Metric
R5: 100R; R_0805_2012Metric
R6, R7, R8, R9: 2k2 pull-up; R_0805_2012Metric
R10: 10R 0.25W branch feed; R_0805_2012Metric
R13, R14: 5k1 1% Rd; R_0805_2012Metric
R15, R16: 0R tuning footprint; R_0805_2012Metric
R17: 10R VDDA filter; R_0805_2012Metric
R18, R19: 100k 1%; R_0805_2012Metric
R20: 0R PC shell bond; R_0805_2012Metric
R21: 10k reset pull-up; R_0805_2012Metric
R22: 10k boot pull-down; R_0805_2012Metric
R23: 10k button pull-up; R_0805_2012Metric
R24: 1k LED limiter; R_0805_2012Metric
R25: 100k enable pull-down; R_0805_2012Metric
R26: 10k override limiter; R_0805_2012Metric
SW1: RESET pushbutton; SW_SPST_TL3342
SW2: BOOT pushbutton; SW_SPST_TL3342
SW3: USER pushbutton; SW_SPST_TL3342
TP1: VBUS_A; TestPoint_Pad_D2.0mm
TP2: VBUS_B; TestPoint_Pad_D2.0mm
TP3: GND_INLINE; TestPoint_Pad_D2.0mm
TP4: CONTACT_A5; TestPoint_Pad_D2.0mm
TP5: CONTACT_B5; TestPoint_Pad_D2.0mm
TP6: INLINE_DP; TestPoint_Pad_D2.0mm
TP7: INLINE_DM; TestPoint_Pad_D2.0mm
TP8: CONTACT_A8; TestPoint_Pad_D2.0mm
TP9: CONTACT_B8; TestPoint_Pad_D2.0mm
TP10: ALERT: floating scope only; TestPoint_Pad_D2.0mm
U1: INA228AIDGSR; VSSOP-10_3x3mm_P0.5mm
U2: ISO1641BD; SOIC-8_3.9x4.9mm_P1.27mm
U3: STM32F072CBT6 / 128K flash; LQFP-48_7x7mm_P0.5mm
U4: TPS7A4333DGQR; HVSSOP10_DGQ
U5: TLV75533PDBVR; SOT-23-5
U6: USBLC6-2SC6; SOT-23-6
U7: TPS22919DCKR; SOT-363_SC-70-6

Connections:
3V3_INLINE: C3.1, C4.1, J6.2, JP1.2, R8.2, R9.2, U1.6 (VS), U2.8 (VCC2)
3V3_INLINE_LDO: C7.1, JP1.1, U4.1 (OUT)
3V3_ISO_PC: C5.1, C19.1, J5.2, R6.2, R7.2, U2.1 (VCC1), U7.5 (QOD), U7.6 (VOUT)
3V3_PC: C9.1, C11.1, C12.1, C13.1, C14.1, C18.1, J9.1 (VTref), J10.4, J11.2, JP4.1, R17.1, R21.1, R23.1, SW2.2, U3.1 (VBAT), U3.24 (VDD), U3.36 (VDDIO2), U3.48 (VDD), U5.5 (OUT), U7.1 (IN)
ALERT_INLINE: TP10.1, U1.3 (ALERT)
BOOT0_PC: R22.1, SW2.1, U3.44 (BOOT0)
BUTTON_PC: R23.2, SW3.1, U3.18 (PB0)
CONTACT_A2: J1.A2, P1.A2
CONTACT_A3: J1.A3, P1.A3
CONTACT_A5: J1.A5, P1.A5, TP4.1
CONTACT_A8: J1.A8, P1.A8, TP8.1
CONTACT_A10: J1.A10, P1.A10
CONTACT_A11: J1.A11, P1.A11
CONTACT_B2: J1.B2, P1.B2
CONTACT_B3: J1.B3, P1.B3
CONTACT_B5: J1.B5, P1.B5, TP5.1
CONTACT_B8: J1.B8, P1.B8, TP9.1
CONTACT_B10: J1.B10, P1.B10
CONTACT_B11: J1.B11, P1.B11
EXT_3V3_INLINE: J7.1, JP1.3
GND_INLINE: C2.2, C3.2, C4.2, C6.2, C7.2, C20.2, C21.2, J1.A1, J1.A12, J1.B1, J1.B12, J2.2, J3.2, J4.4, J6.1, J7.2, P1.A1, P1.A12, P1.B1, P1.B12, R2.2, TP3.1, U1.1 (A1), U1.2 (A0), U1.7 (GND), U2.5 (GND2), U4.4 (MVSEL1), U4.5 (GND), U4.7 (MVSEL2), U4.11 (EP)
GND_PC: C5.2, C8.2, C9.2, C10.2, C11.2, C12.2, C13.2, C14.2, C15.2, C16.2, C17.2, C18.2, C19.2, D1.1 (K), J5.1, J8.A1, J8.A12, J8.B1, J8.B12, J9.3 (GND), J9.5 (GND), J9.9 (GNDDetect), J10.1, J11.1, R13.2, R14.2, R19.2, R20.2, R22.2, R25.2, SW1.2, SW3.2, U2.4 (GND1), U3.8 (VSSA), U3.23 (VSS), U3.35 (VSS), U3.47 (VSS), U5.2 (GND), U6.2 (GND), U7.2 (GND)
GPIO_PA4: J11.3, U3.14 (PA4)
GPIO_PA5: J11.4, U3.15 (PA5)
GPIO_PA6: J11.5, U3.16 (PA6)
GPIO_PA7: J11.6, U3.17 (PA7)
GPIO_PB10: J11.7, U3.21 (PB10)
GPIO_PB11: J11.8, U3.22 (PB11)
INLINE_DM: J1.A7, J1.B7, P1.A7, TP7.1
INLINE_DP: J1.A6, J1.B6, P1.A6, TP6.1
INLINE_FEED: JP3.2, R10.1
INLINE_LDO_IN: C6.1, R10.2, U4.10 (IN)
INLINE_MID: C20.1, C21.1, U4.8 (MID_OUT)
ISO_EN_PC: R25.1, R26.2, U3.11 (PA1), U7.3 (ON)
ISO_FORCE_PC: JP4.2, R26.1
LED_ANODE_PC: D1.2 (A), R24.2
LED_PC: R24.1, U3.19 (PB1)
NRST_PC: C17.1, J9.10 (nRESET), R21.2, SW1.1, U3.7 (NRST)
PC_5V_LDO: C8.1, JP2.2, U5.1 (IN), U5.3 (EN)
PC_CC1: J8.A5, R13.1
PC_CC2: J8.B5, R14.1
PC_DM_CONN: J8.A7, J8.B7, R16.1, U6.3 (IO2), U6.4 (IO2)
PC_DP_CONN: J8.A6, J8.B6, R15.1, U6.1 (IO1), U6.6 (IO1)
PC_VBUS_DETECT: R18.2, R19.1, U3.10 (PA0)
SCL_INLINE: J6.3, R9.1, U1.5 (SCL), U2.6 (SCL2)
SCL_PC: J5.3, R7.1, U2.3 (SCL1), U3.42 (PB6)
SDA_INLINE: J6.4, R8.1, U1.4 (SDA), U2.7 (SDA2)
SDA_PC: J5.4, R6.1, U2.2 (SDA1), U3.43 (PB7)
SHIELD_INLINE: J1.S (SHIELD), P1.S (SHIELD), R2.1
SHIELD_PC: J8.S (SHIELD), R20.1
SHUNT_MINUS: C1.2, R4.2, U1.9 (IN-)
SHUNT_PLUS: C1.1, R3.2, U1.10 (IN+)
SHUNT_SA: J4.1, R1.3 (E1), R3.1
SHUNT_SB: J4.2, R1.4 (E2), R4.1
SWCLK_PC: J9.4 (SWCLK), U3.37 (PA14)
SWDIO_PC: J9.2 (SWDIO), U3.34 (PA13)
UART_RX_PC: J10.3, U3.13 (PA3)
UART_TX_PC: J10.2, U3.12 (PA2)
USB_DM_MCU: R16.2, U3.32 (PA11)
USB_DP_MCU: R15.2, U3.33 (PA12)
VBUS_A: J1.A4, J1.A9, J1.B4, J1.B9, J2.1, JP3.1, R1.1 (I1), TP1.1
VBUS_B: J3.1, J4.3, P1.A4, P1.A9, P1.B4, P1.B9, R1.2 (I2), R5.1, TP2.1
VBUS_FILTER: C2.1, R5.2, U1.8 (VBUS)
VBUS_PC: C10.1, J8.A4, J8.A9, J8.B4, J8.B9, JP2.1, R18.1, U6.5 (VBUS)
VDDA_PC: C15.1, C16.1, R17.2, U3.9 (VDDA)

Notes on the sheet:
01 THROUGH POWER
02 MEASUREMENT
Kelvin current + output voltage
03 INLINE SUPPLY
Taken upstream of the shunt
05 REPORTING USB
06 ACQUISITION + FIRMWARE
07 PC SUPPLY + SUSPEND
04 ISOLATED I²C
POWER WIDGET
BENCH REVISION A / CANONICAL SINGLE-SHEET SCHEMATIC
28 V / 9 A target; selected USB population: 5 A MAX
INLINE | ISOLATED PC
NATIVE KiCad / 82 physical components / 65 named nets / one sheet
Dot = junction. Undotted crossing = no connection. Comma-separated pins share a net. Cross = deliberately unconnected pin.
Each physical component appears once. Both grounds remain separate. Engineering draft; not qualified hardware.
JP1: ONE shunt, 1-2 normal / 2-3 external. JP2 and JP3 fitted. JP4 not fitted.
Canonical source: power-widget-bench.kicad_sch. Previews exported directly by kicad-cli.
Edit the native schematic. Do not rebuild it from a documentation diagram.
ONE COMPLETE PATH
J1: charger / P1: device
Each contact appears once.
Only VBUS crosses R1.
Other contacts pass through.
FOUR-TERMINAL SHUNT
Force pins carry the load.
Kelvin pins sense the drop.
Follow both sense wires
to the INA228 inputs.
